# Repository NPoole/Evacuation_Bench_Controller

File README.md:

# Evacuation_Bench_Controller
Big dumb 19" rackmount PCB for controlling and monitoring the state of my High-Vacuum workbench

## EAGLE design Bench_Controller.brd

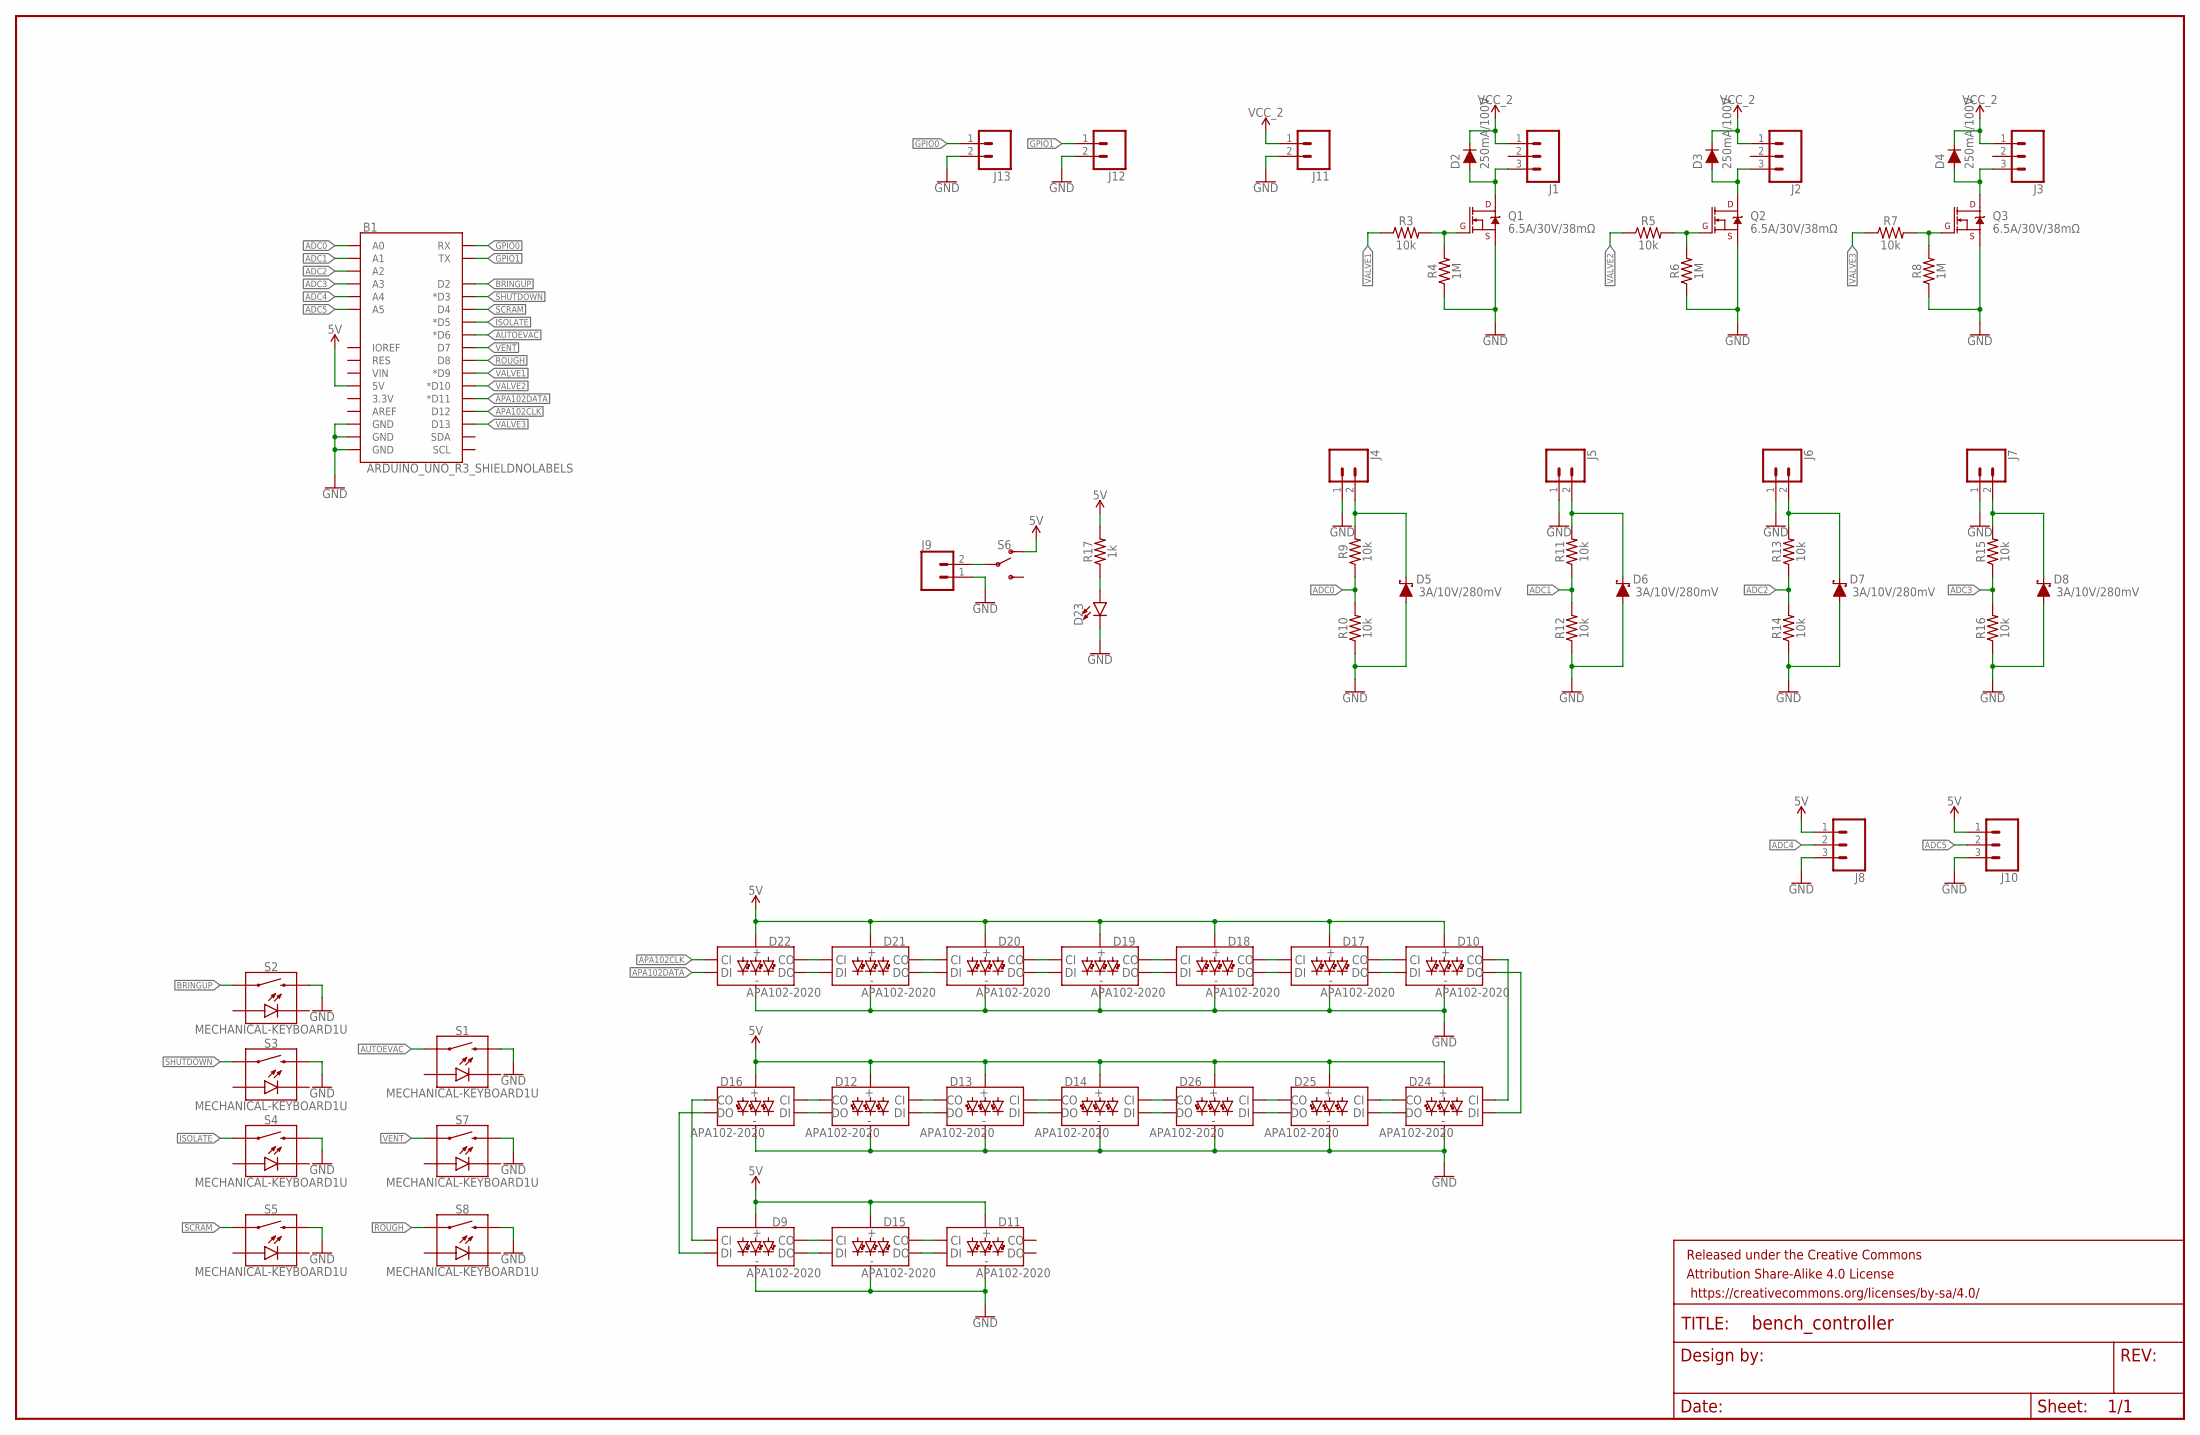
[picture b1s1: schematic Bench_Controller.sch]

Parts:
B1: ARDUINO_UNO_R3_SHIELDNOLABELS; UNO_R3_SHIELD_NOLABELS
D2, D3, D4: 250mA/100V; SOD-323
D5, D6, D7, D8: 3A/10V/280mV; SOD-323
D9, D10, D11, D12, D13, D14, D15, D16, D17, D18, D19, D20, D21, D22, D24, D25, D26: APA102-2020
D23: LED5MM; LED_5MM
FRAME1: FRAME-LEDGER; CREATIVE_COMMONS
J1, J2, J3, J8, J10: CONN_031X03_NO_SILK; 1X03_NO_SILK
J4, J5, J6, J7, J9, J11, J12, J13: CONN_021X02_NO_SILK; 1X02_NO_SILK
Q1, Q2, Q3: 6.5A/30V/38mΩ; SO08
R3, R5, R7, R9, R10, R11, R12, R13, R14, R15, R16: 10k; 0603
R4, R6, R8: 1M; 0603
R17: 1k; 0603
S1, S2, S3, S4, S5, S7, S8: MECHANICAL-KEYBOARD1U; CHERRY-MX-LED-1U
S6: SWITCH-SPDT-PTH-11.6X4.0MM; SWITCH_SPDT_PTH_11.6X4.0MM

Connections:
5V: B1.5V, D9.VDD (VCC), D10.VDD (VCC), D11.VDD (VCC), D12.VDD (VCC), D13.VDD (VCC), D14.VDD (VCC), D15.VDD (VCC), D16.VDD (VCC), D17.VDD (VCC), D18.VDD (VCC), D19.VDD (VCC), D20.VDD (VCC), D21.VDD (VCC), D22.VDD (VCC), D24.VDD (VCC), D25.VDD (VCC), D26.VDD (VCC), J8.1, J10.1, R17.2, S6.1 (O)
ADC0: B1.A0, R9.1, R10.2
ADC1: B1.A1, R11.1, R12.2
ADC2: B1.A2, R13.1, R14.2
ADC3: B1.A3, R15.1, R16.2
ADC4: B1.A4, J8.2
ADC5: B1.A5, J10.2
ANALOG_IN_0: D5.C, J4.2, R9.2
ANALOG_IN_1: D6.C, J5.2, R11.2
ANALOG_IN_2: D7.C, J6.2, R13.2
ANALOG_IN_3: D8.C, J7.2, R15.2
APA102CLK: B1.D12, D22.CKI (CI)
APA102DATA: B1.D11 (*D11), D22.SDI (DI)
AUTOEVAC: B1.D6 (*D6), S1.S1 (1)
BRINGUP: B1.D2, S2.S1 (1)
GND: B1.GND@0 (GND), B1.GND@1 (GND), B1.GND@2 (GND), D5.A, D6.A, D7.A, D8.A, D9.GND, D10.GND, D11.GND, D12.GND, D13.GND, D14.GND, D15.GND, D16.GND, D17.GND, D18.GND, D19.GND, D20.GND, D21.GND, D22.GND, D23.K (C), D24.GND, D25.GND, D26.GND, J4.1, J5.1, J6.1, J7.1, J8.3, J9.1, J10.3, J11.2, J12.2, J13.2, Q1.1 (S), Q1.2 (S), Q1.3 (S), Q2.1 (S), Q2.2 (S), Q2.3 (S), Q3.1 (S), Q3.2 (S), Q3.3 (S), R4.1, R6.1, R8.1, R10.1, R12.1, R14.1, R16.1, S1.S2 (2), S2.S2 (2), S3.S2 (2), S4.S2 (2), S5.S2 (2), S7.S2 (2), S8.S2 (2)
GPIO0: B1.RX, J13.1
GPIO1: B1.TX, J12.1
ISOLATE: B1.D5 (*D5), S4.S1 (1)
unnamed: Q1.4 (G), R3.2, R4.2
unnamed: Q2.4 (G), R5.2, R6.2
unnamed: D2.A, J1.3, Q1.5 (D), Q1.6 (D), Q1.7 (D), Q1.8 (D)
unnamed: D3.A, J2.3, Q2.5 (D), Q2.6 (D), Q2.7 (D), Q2.8 (D)
unnamed: Q3.4 (G), R7.2, R8.2
unnamed: D4.A, J3.3, Q3.5 (D), Q3.6 (D), Q3.7 (D), Q3.8 (D)
unnamed: D21.CKI (CI), D22.CKO (CO)
unnamed: J9.2, S6.2
unnamed: D23.A, R17.1
unnamed: D21.SDI (DI), D22.SDO (DO)
unnamed: D20.CKI (CI), D21.CKO (CO)
unnamed: D20.SDI (DI), D21.SDO (DO)
unnamed: D19.CKI (CI), D20.CKO (CO)
unnamed: D19.SDI (DI), D20.SDO (DO)
unnamed: D18.CKI (CI), D19.CKO (CO)
unnamed: D18.SDI (DI), D19.SDO (DO)
unnamed: D17.CKI (CI), D18.CKO (CO)
unnamed: D17.SDI (DI), D18.SDO (DO)
unnamed: D10.CKI (CI), D17.CKO (CO)
unnamed: D10.SDI (DI), D17.SDO (DO)
unnamed: D10.CKO (CO), D24.CKI (CI)
unnamed: D10.SDO (DO), D24.SDI (DI)
unnamed: D24.CKO (CO), D25.CKI (CI)
unnamed: D24.SDO (DO), D25.SDI (DI)
unnamed: D25.CKO (CO), D26.CKI (CI)
unnamed: D25.SDO (DO), D26.SDI (DI)
unnamed: D14.CKI (CI), D26.CKO (CO)
unnamed: D14.SDI (DI), D26.SDO (DO)
unnamed: D13.CKI (CI), D14.CKO (CO)
unnamed: D13.SDI (DI), D14.SDO (DO)
unnamed: D12.CKI (CI), D13.CKO (CO)
unnamed: D12.SDI (DI), D13.SDO (DO)
unnamed: D12.CKO (CO), D16.CKI (CI)
unnamed: D12.SDO (DO), D16.SDI (DI)
unnamed: D9.CKI (CI), D16.CKO (CO)
unnamed: D9.SDI (DI), D16.SDO (DO)
unnamed: D9.CKO (CO), D15.CKI (CI)
unnamed: D9.SDO (DO), D15.SDI (DI)
unnamed: D11.CKI (CI), D15.CKO (CO)
unnamed: D11.SDI (DI), D15.SDO (DO)
ROUGH: B1.D8, S8.S1 (1)
SCRAM: B1.D4, S5.S1 (1)
SHUTDOWN: B1.D3 (*D3), S3.S1 (1)
VALVE1: B1.D9 (*D9), R3.1
VALVE2: B1.D10 (*D10), R5.1
VALVE3: B1.D13, R7.1
VCC_2: D2.C, D3.C, D4.C, J1.1, J2.1, J3.1, J11.1
VENT: B1.D7, S7.S1 (1)

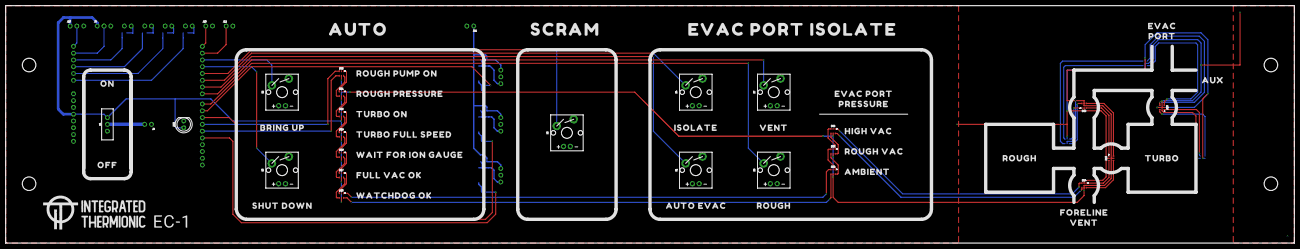
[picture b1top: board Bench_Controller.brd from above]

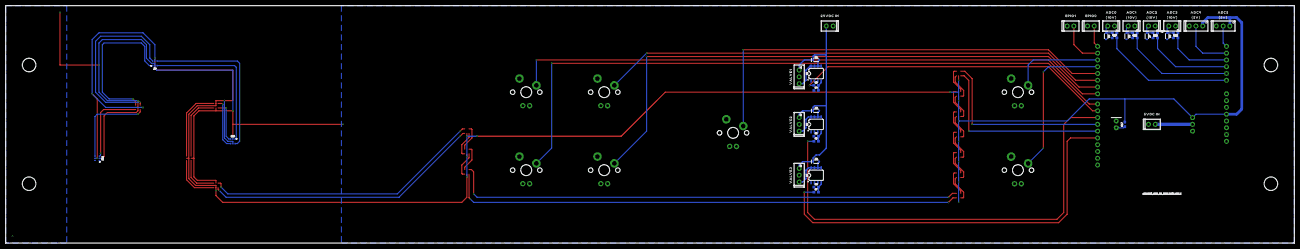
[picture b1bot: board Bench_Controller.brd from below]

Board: 2 copper layers, 482.6 x 88.9 mm, 117 parts (55 on the bottom side), 67 nets.

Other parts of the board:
U$1, U$25: ROUGH0
U$2: TURBO0
U$3: FORELINE0
U$4, U$24: VENT0
U$5: EVAC0
U$6: PORT0
U$7: AUX0
U$8: ON0
U$9: OFF0
U$10: AUTO0
U$11: BRING_UP0
U$12: SHUT_DOWN0
U$13: SCRAM0
U$14: EVAC_PORT_ISOLATE0
U$15: FULL_VAC_OK0
U$16: ROUGH_PRESSURE0
U$17: TURBO_ON0
U$18: ROUGH_PUMP_ON0
U$19: TURBO_FULL_SPEED0
U$20: WATCHDOG_OK0
U$21: WAIT_FOR_ION_GAUGE0
U$22: ISOLATE0
U$23: AUTO_EVAC0
U$26: EVAC_PORT0
U$27: PRESSURE0
U$28: HIGH_VAC0
U$29: ROUGH_VAC0
U$30: AMBIENT0
U$31: ADC50
U$32: ADC40
U$33: ADC30
U$34: ADC20
U$35: ADC10
U$36: ADC00
U$37: GPIO00
U$38: GPIO10
U$39: 5VDC_IN0
U$40, U$41: _##5V##_0
U$42, U$43, U$44, U$45: _##10V##_0
U$46: 24VDC_IN0
U$47: VALVE10
U$48: VALVE20
U$49: VALVE30
U$50: INTEG#SVG0
U$51: EC#10

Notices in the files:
parts and their libraries:
SparkFun-DiscreteSemi: Licensing: Creative Commons ShareAlike 4.0 International - https://creativecommons.org/licenses/by-sa/4.0
SparkFun-Aesthetics: Released under the Creative Commons Attribution Share-Alike 4.0 License
SparkFun-Aesthetics: https://creativecommons.org/licenses/by-sa/4.0
